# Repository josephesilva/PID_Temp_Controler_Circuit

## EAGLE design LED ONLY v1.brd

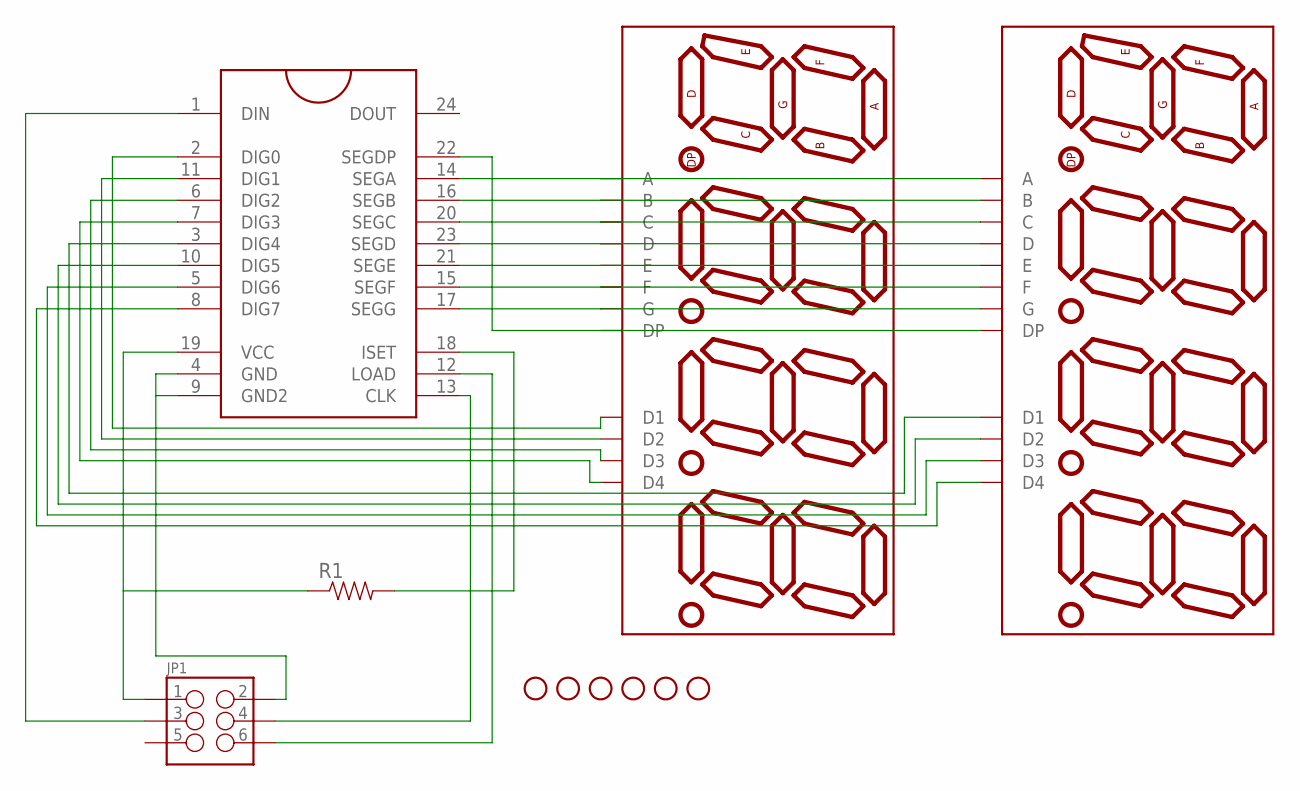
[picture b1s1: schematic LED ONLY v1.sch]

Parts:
JP1: M03X2; 2X3-SHROUDED
R1: RESISTORPTH-1/4W; AXIAL-0.4
STANDOFF1, STANDOFF2, STANDOFF3, STANDOFF4, STANDOFF5, STANDOFF6: STAND-OFF
U$3: MAX7219DIP; DIL24
U$4, U$5: 7-SEGMENT-4DIGIT-COUNTERPTH; 7-SEGMENT-4DIGIT-COUNTER

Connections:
unnamed: U$3.14 (SEGA), U$4.11 (A), U$5.11 (A)
unnamed: U$3.16 (SEGB), U$4.7 (B), U$5.7 (B)
unnamed: U$3.20 (SEGC), U$4.4 (C), U$5.4 (C)
unnamed: U$3.23 (SEGD), U$4.2 (D), U$5.2 (D)
unnamed: U$3.21 (SEGE), U$4.1 (E), U$5.1 (E)
unnamed: U$3.15 (SEGF), U$4.10 (F), U$5.10 (F)
unnamed: U$3.17 (SEGG), U$4.5 (G), U$5.5 (G)
unnamed: U$3.22 (SEGDP), U$4.3 (DP), U$5.3 (DP)
unnamed: U$3.2 (DIG0), U$4.12 (D1)
unnamed: U$3.11 (DIG1), U$4.9 (D2)
unnamed: U$3.6 (DIG2), U$4.8 (D3)
unnamed: U$3.7 (DIG3), U$4.6 (D4)
unnamed: JP1.1, R1.P$1 (1), U$3.19 (VCC)
unnamed: JP1.2, U$3.4 (GND), U$3.9 (GND2)
unnamed: U$3.3 (DIG4), U$5.12 (D1)
unnamed: U$3.10 (DIG5), U$5.9 (D2)
unnamed: U$3.5 (DIG6), U$5.8 (D3)
unnamed: U$3.8 (DIG7), U$5.6 (D4)
unnamed: R1.P$2 (2), U$3.18 (ISET)
unnamed: JP1.3, U$3.1 (DIN)
unnamed: JP1.6, U$3.12 (LOAD)
unnamed: JP1.4, U$3.13 (CLK)

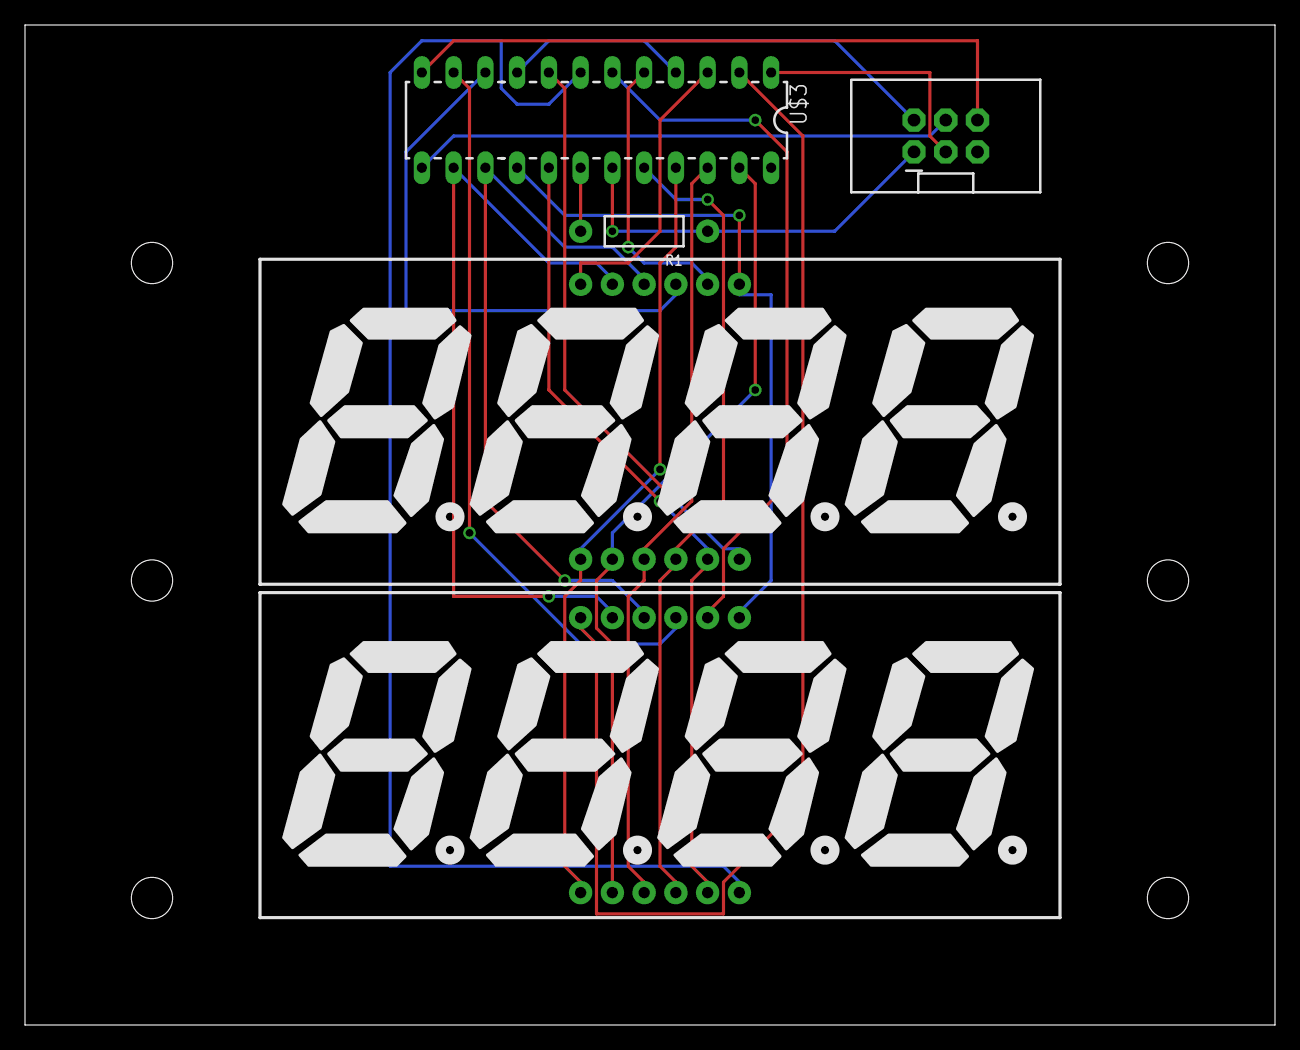
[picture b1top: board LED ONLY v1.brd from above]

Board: 2 copper layers, 100.0 x 80.0 mm, 11 parts (0 on the bottom side), 22 nets.

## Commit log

2016-02-02 Holds pid controler eagle files.

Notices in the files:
parts and their libraries:
SparkFun-DigitalIC: Licensing: CC v3.0 Share-Alike You are welcome to use this library for commercial purposes.
